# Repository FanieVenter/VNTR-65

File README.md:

# VNTR-65

A custom, over-engineered 65% keyboard featuring an RP2350 MCU, a hall effect key matrix, an analog slide potentiometer, and an OLED display. Built for daily use thanks to Hack Club.

## Why I decided to make this keyboard.
I wanted to build a nice keyboard that I could use every day at school while knowing it won't break, I also wanted to make a keyboard that used hall effect switches to allow for analog inputs in racing ganes like Assetto Corsa and giving me a more challenging and fun experience designing it.

## How to use it.
To use this keyboard you will need to either download the production files for JLCPCB or create your own by exporting it them from Kicad. You will then need to place a order for the PCB using the productions files at your chosen pcb manufacturer. After you have received the PCB you will need to solder all the components onto the PCB and then flash the firmware onto the RP2350. While this is happening you can either 3d print the case or get it milled out of aluminum and wood. After you have the case and the PCB ready you can then assemble the keyboard and upload the firmware to the RP2350 and then you can use it. 

## What I learnt with this project.
I learn't how to design a keyboard from scratch using Kicad for the pcb. I also learn't how to use onshape after deciding to swap to it from Freecad a little bit because the projects says to have it in onshape but mostly as I had realised after 2 years of FreeCAD use that it wasn't powerful enough for me. I learn't how to take a raw wood texture file and make it look like a satin polyeuranted finished piece of wood in blender.
# Important.
The cost of the pcba has gone down since I submitted the project for review. For updated pricing and screenshot check the [BOM](BOM.pdf).

## Onshape Link
Onshape link for the [Case](https://cad.onshape.com/documents/299d1cd18e1c0fa7ad37c188/w/39af968ec4536d8e3dda6814/e/b83c5326b9acf81a68bd5a35?renderMode=0&uiState=6a509a3fdb7545b8e7caa558).

## Files
- [Journal](Journal.md) Journal of this project.
- [PCB Files](Hardware/PCB) Kicad files for the keyboard.
- [Production Files](Hardware/PCB/production) Production files for this project.
- [3D Files](Hardware/3D%20Models) 3D models used in this project as well as where the blender file is.
- [Gallery](Gallery.md) Images of the project and renders of the keyboard.
- [BOM (PDF)](BOM.pdf) Bill of materials.
- [BOM (CSV)](BOM.csv) Bill of materials in CSV format.

## Schematic-Main

*Main schematic.*  

## Schematic-Switch

*Hall effect switch matrix.*

## PCB Photos

*Front and back of the PCB — the back has the silkscreen applied.*

## Wiring

*Full PCB wiring across all copper layers.*

*Full PCB wiring on the front copper layer.*

*Full PCB wiring on the back copper layer.*

*Main section wiring on the front copper layer.*

*Main section wiring on the back copper layer.*

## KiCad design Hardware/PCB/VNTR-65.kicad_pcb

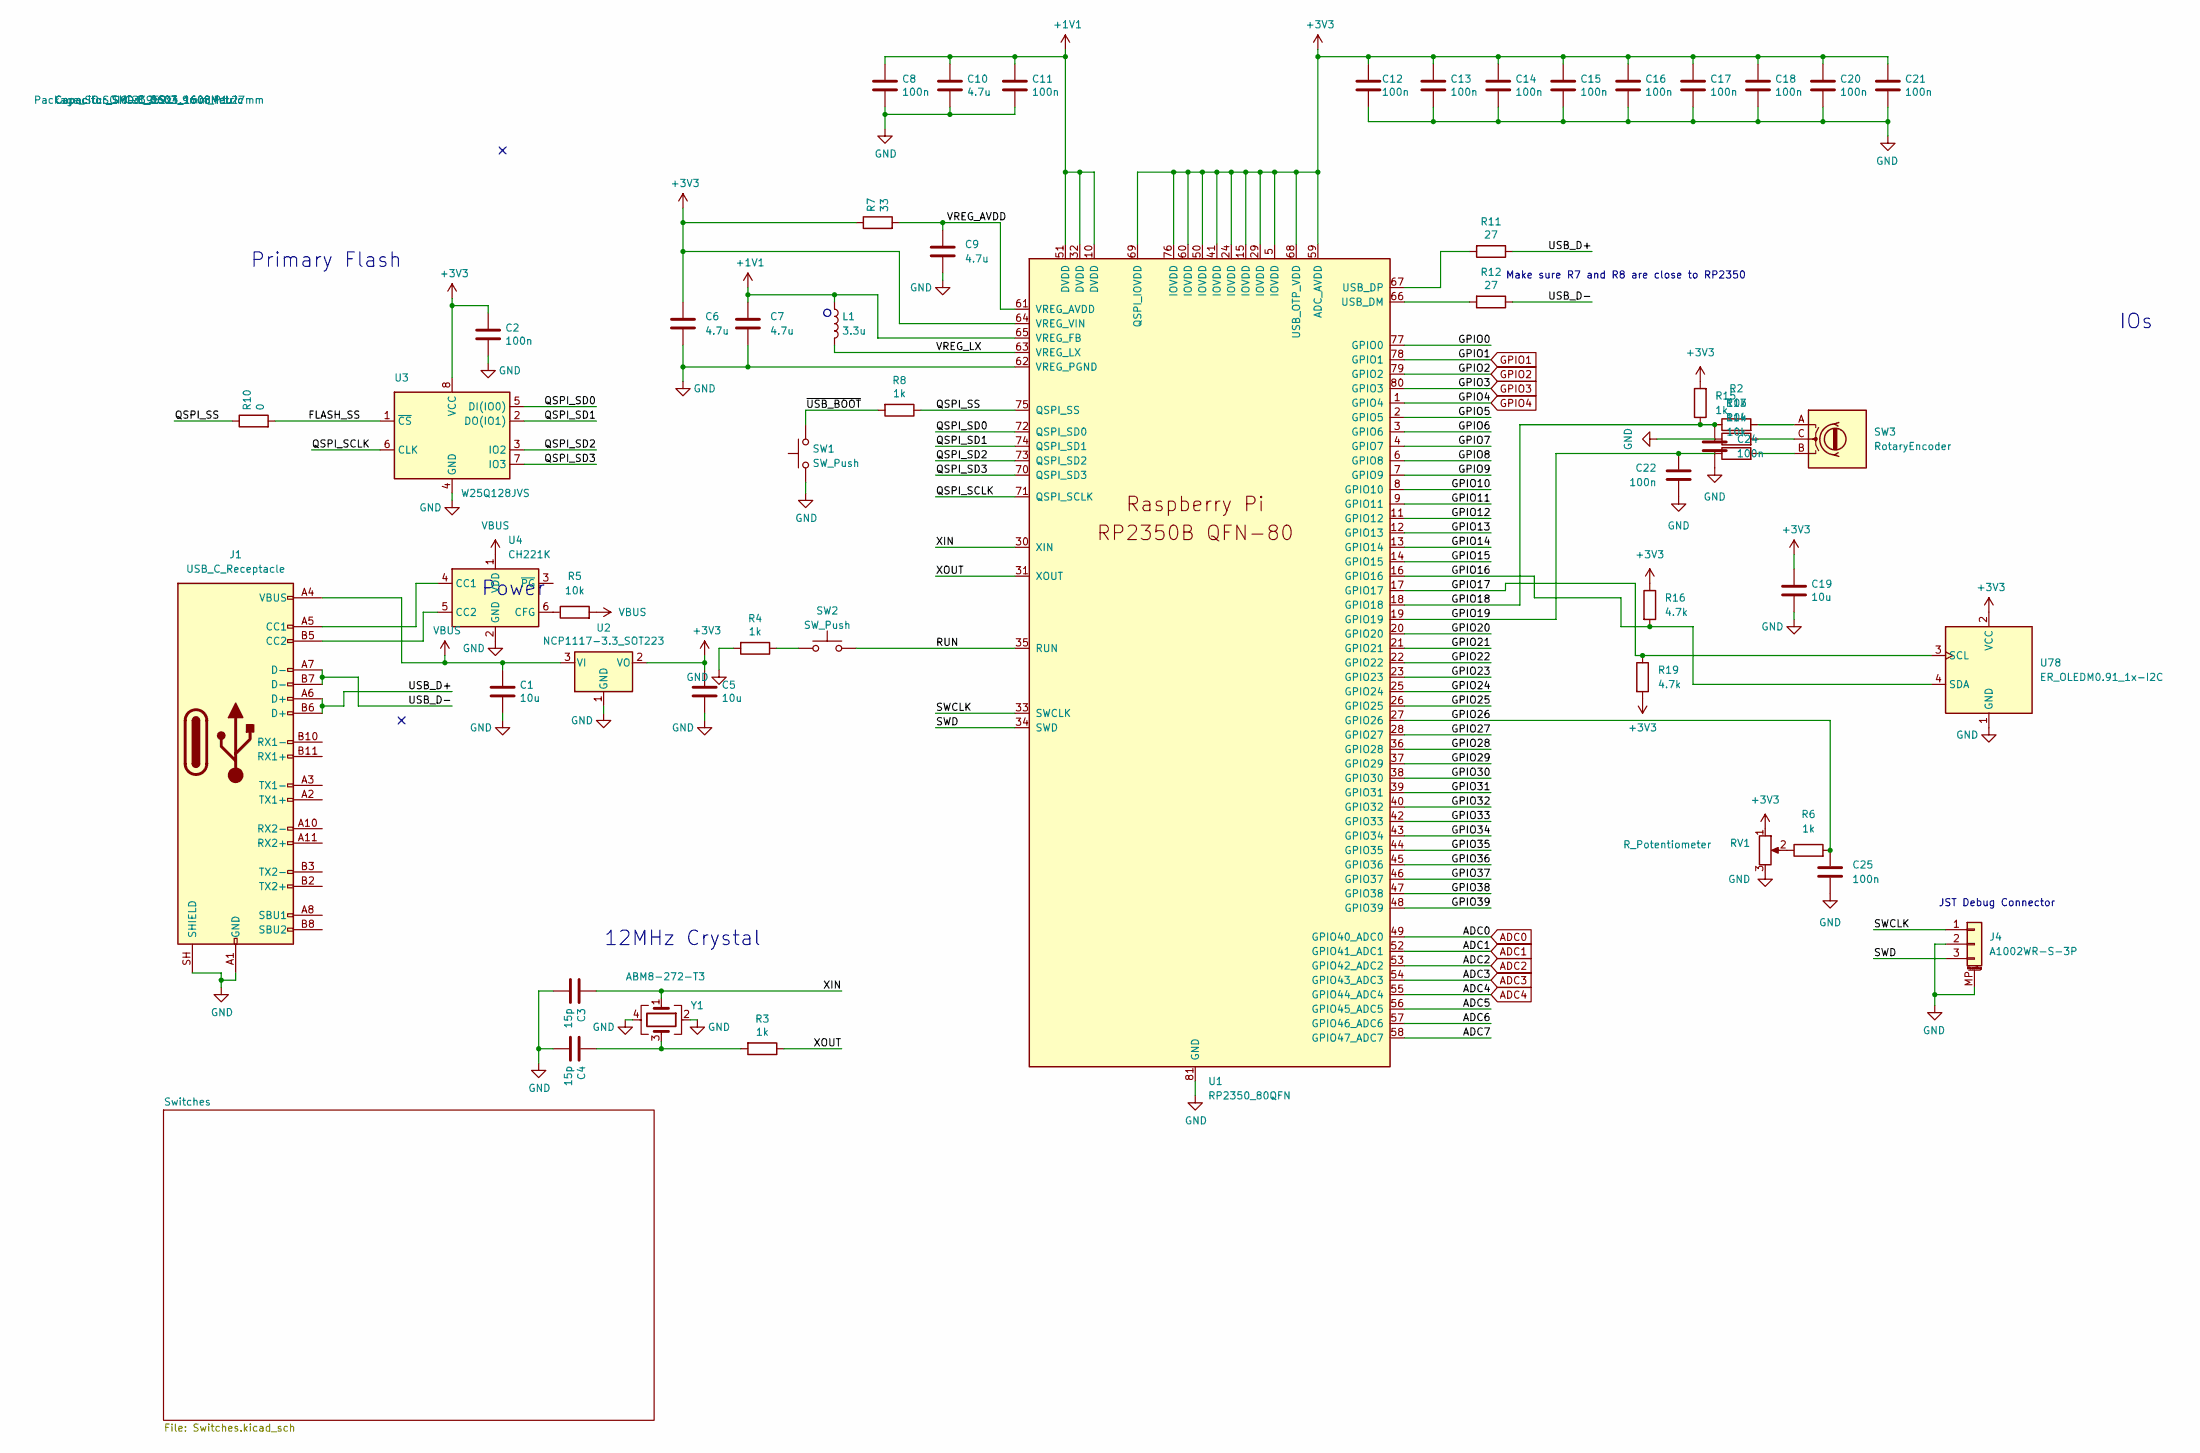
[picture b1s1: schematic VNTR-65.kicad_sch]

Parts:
C1, C5, C19: 10u; C_0603_1608Metric
C2, C8, C11, C12, C13, C14, C15, C16, C17, C18, C20, C21, C22, C24, C25: 100n; C_0603_1608Metric
C3, C4: 15p; C_0603_1608Metric
C6, C7, C9, C10: 4.7u; C_0603_1608Metric
J1: USB_C_Receptacle; USB_C_Receptacle_Amphenol_12401610E4-2A
J4: A1002WR-S-3P; JST_SH_SM03B-SRSS-TB_1x03-1MP_P1.00mm_Horizontal; LCSC Part # C239521
L1: 3.3u; L_pol_2016
R2, R5, R13, R14: 10k; R_0603_1608Metric
R3, R4, R6, R8, R15: 1k; R_0603_1608Metric
R7: 33; R_0603_1608Metric
R10: 0; R_0603_1608Metric
R11, R12: 27; R_0603_1608Metric
R16, R19: 4.7k; R_0603_1608Metric
RV1: R_Potentiometer; Potentiometer_Bourns_PTA6043_Single_Slide
SW1, SW2: SW_Push; SW_Push_1P1T_NO_Vertical_Wuerth_434133025816
SW3: RotaryEncoder; RotaryEncoder_Alps_EC11E-Switch_Vertical_H20mm
U1: RP2350_80QFN; QFN-80-1EP_10x10mm_P0.4mm_EP3.4x3.4mm
U2: NCP1117-3.3_SOT223; SOT-223-3_TabPin2
U3: W25Q128JVS; SOIC-8_3.9x4.9mm_P1.27mm
U4: CH221K; SOT-23-6
U78: ER_OLEDM0.91_1x-I2C
Y1: ABM8-272-T3; Crystal_SMD_3225-4Pin_3.2x2.5mm

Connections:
+1V1: C7.1, C8.1, C10.1, C11.1, L1.1, U1.10 (DVDD), U1.32 (DVDD), U1.51 (DVDD), U1.65 (VREG_FB)
+3V3: C2.1, C5.1, C6.1, C12.1, C13.1, C14.1, C15.1, C16.1, C17.1, C18.1, C19.1, C20.1, C21.1, R7.1, R15.2, R16.1, R19.2, RV1.1, U1.5 (IOVDD), U1.15 (IOVDD), U1.24 (IOVDD), U1.29 (IOVDD), U1.41 (IOVDD), U1.50 (IOVDD), U1.59 (ADC_AVDD), U1.60 (IOVDD), U1.64 (VREG_VIN), U1.68 (USB_OTP_VDD), U1.69 (QSPI_IOVDD), U1.76 (IOVDD), U2.2 (VO), U3.8 (VCC), U78.2 (VCC); also elsewhere on the board
/ADC5: U1.56 (GPIO45_ADC5)
/ADC6: U1.57 (GPIO46_ADC6)
/ADC7: U1.58 (GPIO47_ADC7)
/FLASH_SS: R10.2, U3.1 (~CS); also elsewhere on the board
/GPIO0: U1.77 (GPIO0); also elsewhere on the board
/GPIO5: U1.2 (GPIO5)
/GPIO6: U1.3 (GPIO6)
/GPIO7: U1.4 (GPIO7)
/GPIO8: U1.6 (GPIO8)
/GPIO9: U1.7 (GPIO9)
/GPIO10: U1.8 (GPIO10)
/GPIO11: U1.9 (GPIO11)
/GPIO12: U1.11 (GPIO12)
/GPIO13: U1.12 (GPIO13)
/GPIO14: U1.13 (GPIO14)
/GPIO15: U1.14 (GPIO15)
/GPIO16: R16.2, U1.16 (GPIO16), U78.4 (SDA)
/GPIO17: R19.1, U1.17 (GPIO17), U78.3 (SCL)
/GPIO18: C24.2, R2.1, R15.1, U1.18 (GPIO18)
/GPIO19: C22.2, R14.1, U1.19 (GPIO19)
/GPIO20: U1.20 (GPIO20)
/GPIO21: U1.21 (GPIO21)
/GPIO22: U1.22 (GPIO22)
/GPIO23: U1.23 (GPIO23)
/GPIO24: U1.25 (GPIO24)
/GPIO25: U1.26 (GPIO25)
/GPIO26: C25.2, R6.2, U1.27 (GPIO26)
/GPIO27: U1.28 (GPIO27)
/GPIO28: U1.36 (GPIO28)
/GPIO29: U1.37 (GPIO29)
/GPIO30: U1.38 (GPIO30)
/GPIO31: U1.39 (GPIO31)
/GPIO32: U1.40 (GPIO32)
/GPIO33: U1.42 (GPIO33)
/GPIO34: U1.43 (GPIO34)
/GPIO35: U1.44 (GPIO35)
/GPIO36: U1.45 (GPIO36)
/GPIO37: U1.46 (GPIO37)
/GPIO38: U1.47 (GPIO38)
/GPIO39: U1.48 (GPIO39)
/QSPI_SCLK: U1.71 (QSPI_SCLK), U3.6 (CLK)
/QSPI_SD0: U1.72 (QSPI_SD0), U3.5 (DI(IO0))
/QSPI_SD1: U1.74 (QSPI_SD1), U3.2 (DO(IO1))
/QSPI_SD2: U1.73 (QSPI_SD2), U3.3 (IO2)
/QSPI_SD3: U1.70 (QSPI_SD3), U3.7 (IO3)
/QSPI_SS: R8.1, R10.1, U1.75 (QSPI_SS)
/RUN: SW2.2, U1.35 (RUN)
/SWCLK: J4.1, U1.33 (SWCLK)
/SWD: J4.3, U1.34 (SWD)
/USB_D+: J1.A6 (D+), J1.B6 (D+), R11.1
/USB_D-: J1.A7 (D-), J1.B7 (D-), R12.1
/VREG_AVDD: C9.1, R7.2, U1.61 (VREG_AVDD)
/VREG_LX: L1.2, U1.63 (VREG_LX)
/XIN: C3.1, U1.30 (XIN), Y1.1
/XOUT: R3.1, U1.31 (XOUT)
/~USB_BOOT: R8.2, SW1.2
ADC0: U1.49 (GPIO40_ADC0); also elsewhere on the board
ADC1: U1.52 (GPIO41_ADC1); also elsewhere on the board
ADC2: U1.53 (GPIO42_ADC2); also elsewhere on the board
ADC3: U1.54 (GPIO43_ADC3); also elsewhere on the board
ADC4: U1.55 (GPIO44_ADC4); also elsewhere on the board
GND: C1.2, C2.2, C3.2, C4.2, C5.2, C6.2, C7.2, C8.2, C9.2, C10.2, C11.2, C12.2, C13.2, C14.2, C15.2, C16.2, C17.2, C18.2, C19.2, C20.2, C21.2, C22.1, C24.1, C25.1, J1.A1 (GND), J1.A12 (GND), J1.B1 (GND), J1.B12 (GND), J1.SH (SHIELD), J4.2, J4.MP (MountPin), R4.2, R13.1, RV1.3, SW1.1, U1.62 (VREG_PGND), U1.81 (GND), U2.1 (GND), U3.4 (GND), U4.2 (GND), U78.1 (GND), Y1.2, Y1.4; also elsewhere on the board
GPIO1: U1.78 (GPIO1); also elsewhere on the board
GPIO2: U1.79 (GPIO2); also elsewhere on the board
GPIO3: U1.80 (GPIO3); also elsewhere on the board
GPIO4: U1.1 (GPIO4); also elsewhere on the board
unnamed: C4.1, R3.2, Y1.3
unnamed: J1.A5 (CC1), U4.4 (CC1)
unnamed: J1.B5 (CC2), U4.5 (CC2)
unnamed: R2.2, SW3.A
unnamed: R4.1, SW2.1
unnamed: R6.1, RV1.2
unnamed: R13.2, SW3.C
unnamed: R14.2, SW3.B
unnamed: R12.2, U1.66 (USB_DM)
unnamed: R11.2, U1.67 (USB_DP)
unnamed: R5.1, U4.6 (CFG)
VBUS: C1.1, J1.A4 (VBUS), J1.A9 (VBUS), J1.B4 (VBUS), J1.B9 (VBUS), R5.2, U2.3 (VI), U4.1 (VDD)

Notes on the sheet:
Make sure R7 and R8 are close to RP2350
JST Debug Connector
Power
12MHz Crystal
IOs
Primary Flash

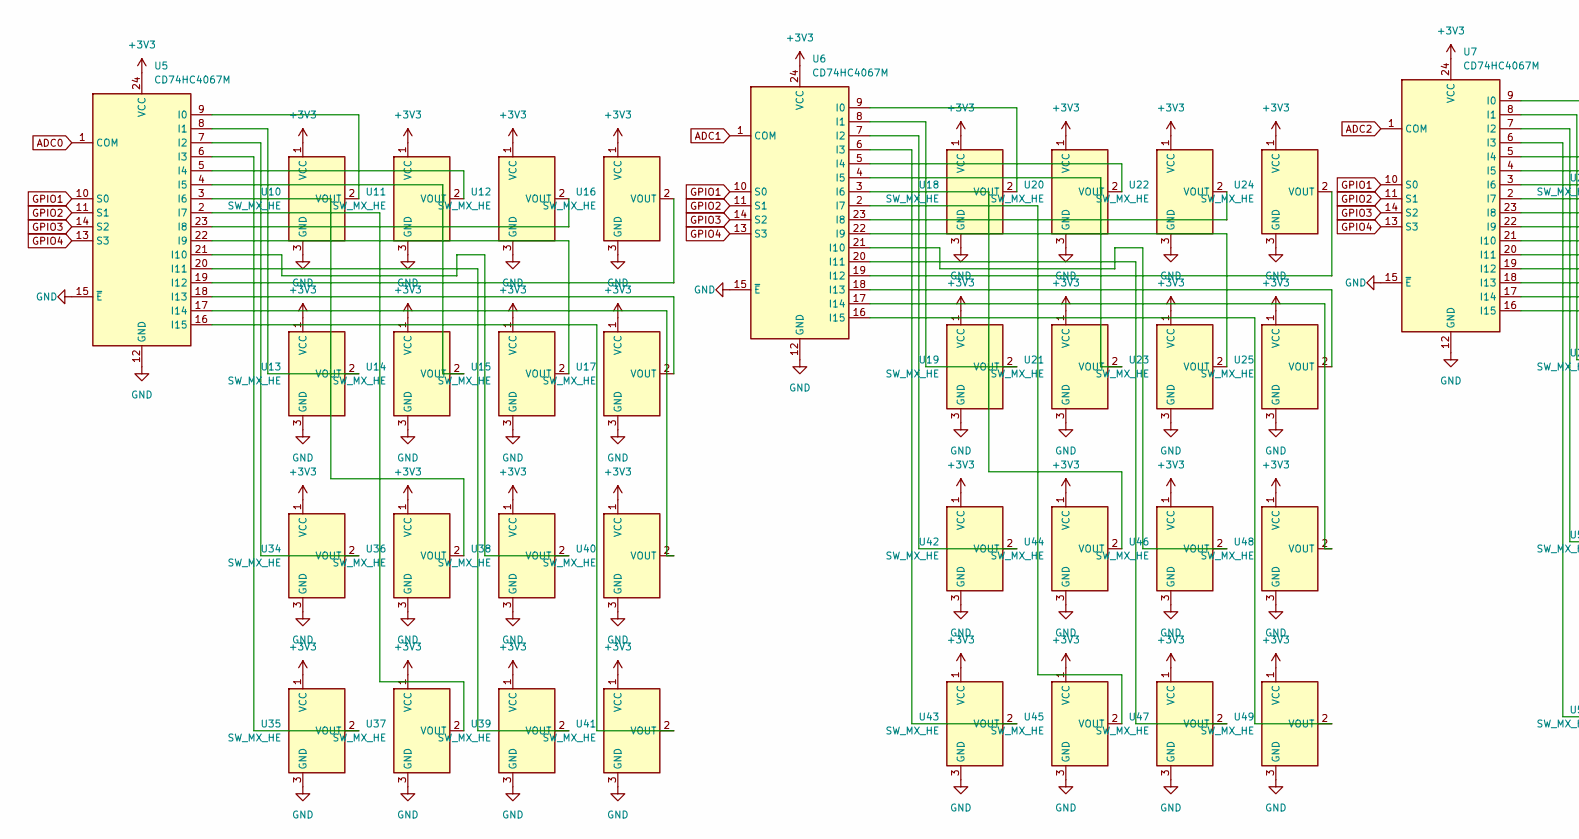
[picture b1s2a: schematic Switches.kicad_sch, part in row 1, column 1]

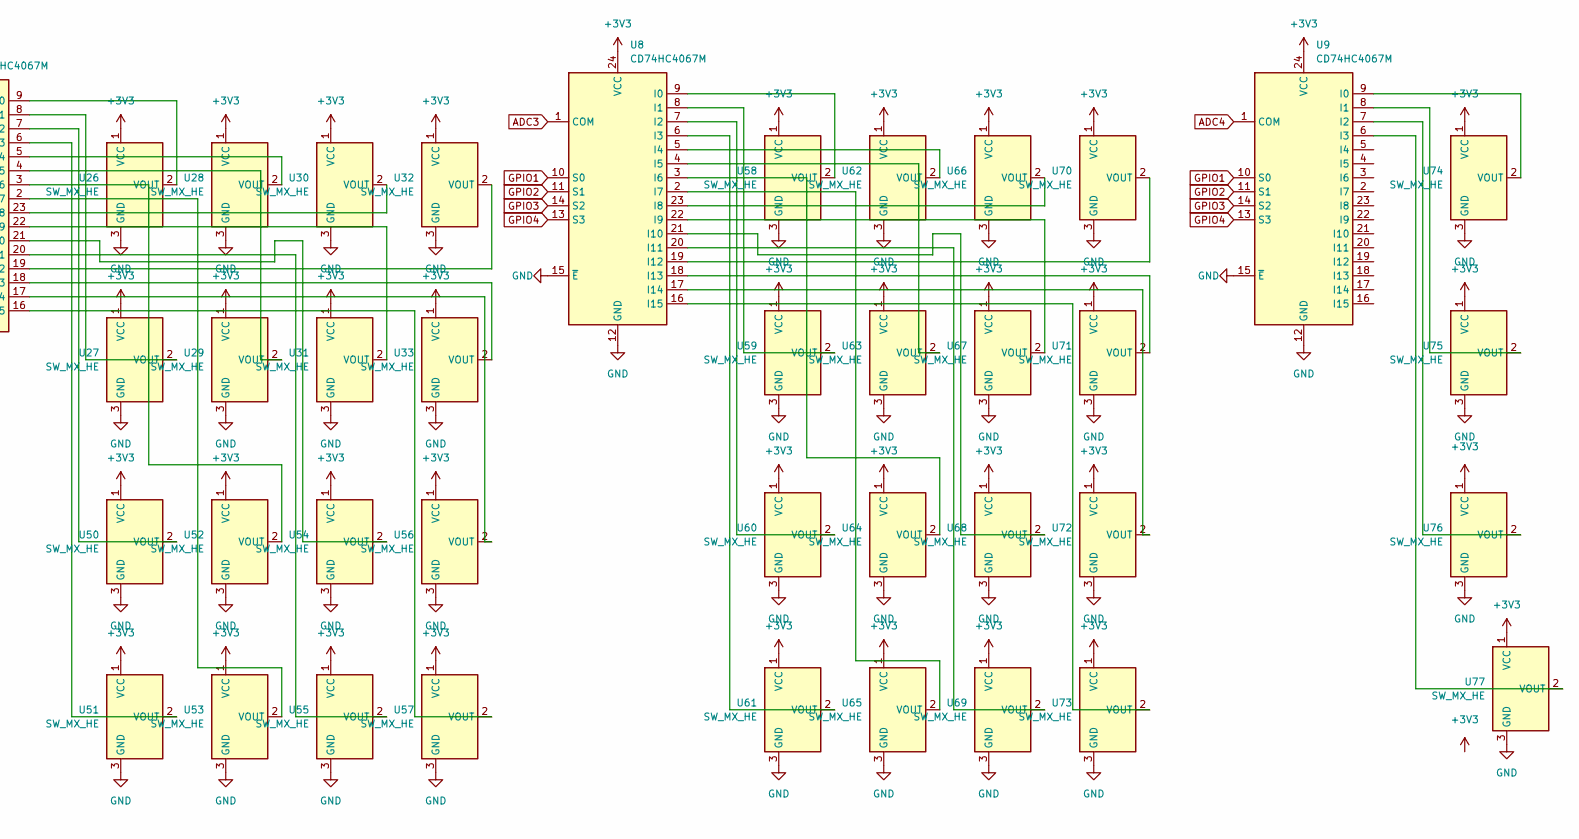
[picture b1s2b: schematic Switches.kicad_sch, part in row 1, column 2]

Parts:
U5, U6, U7, U8, U9: CD74HC4067M; SOIC-24W_7.5x15.4mm_P1.27mm
U10, U11, U12, U13, U14, U15, U16, U17, U18, U19, U20, U21, U22, U23, U24, U25, U26, U27, U28, U29, U30, U31, U32, U33, U34, U35, U36, U37, U38, U39, U40, U41, U42, U43, U44, U45, U46, U47, U48, U49, U50, U51, U52, U53, U54, U55, U56, U57, U58, U59, U60, U61, U62, U63, U64, U65, U66, U67, U68, U69, U70, U71, U72, U73, U74, U75, U76, U77: SW_MX_HE; SW_MX_HE_0deg_1u

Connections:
+3V3: U5.24 (VCC), U6.24 (VCC), U7.24 (VCC), U8.24 (VCC), U9.24 (VCC), U10.1 (VCC), U11.1 (VCC), U12.1 (VCC), U13.1 (VCC), U14.1 (VCC), U15.1 (VCC), U16.1 (VCC), U17.1 (VCC), U18.1 (VCC), U19.1 (VCC), U20.1 (VCC), U21.1 (VCC), U22.1 (VCC), U23.1 (VCC), U24.1 (VCC), U25.1 (VCC), U26.1 (VCC), U27.1 (VCC), U28.1 (VCC), U29.1 (VCC), U30.1 (VCC), U31.1 (VCC), U32.1 (VCC), U33.1 (VCC), U34.1 (VCC), U35.1 (VCC), U36.1 (VCC), U37.1 (VCC), U38.1 (VCC), U39.1 (VCC), U40.1 (VCC), U41.1 (VCC), U42.1 (VCC), U43.1 (VCC), U44.1 (VCC), U45.1 (VCC), U46.1 (VCC), U47.1 (VCC), U48.1 (VCC), U49.1 (VCC), U50.1 (VCC), U51.1 (VCC), U52.1 (VCC), U53.1 (VCC), U54.1 (VCC), U55.1 (VCC), U56.1 (VCC), U57.1 (VCC), U58.1 (VCC), U59.1 (VCC), U60.1 (VCC), U61.1 (VCC), U62.1 (VCC), U63.1 (VCC), U64.1 (VCC), U65.1 (VCC), U66.1 (VCC), U67.1 (VCC), U68.1 (VCC), U69.1 (VCC), U70.1 (VCC), U71.1 (VCC), U72.1 (VCC), U73.1 (VCC), U74.1 (VCC), U75.1 (VCC), U76.1 (VCC), U77.1 (VCC); also elsewhere on the board
ADC0: U5.1 (COM); also elsewhere on the board
ADC1: U6.1 (COM); also elsewhere on the board
ADC2: U7.1 (COM); also elsewhere on the board
ADC3: U8.1 (COM); also elsewhere on the board
ADC4: U9.1 (COM); also elsewhere on the board
GND: U5.12 (GND), U5.15 (~E), U6.12 (GND), U6.15 (~E), U7.12 (GND), U7.15 (~E), U8.12 (GND), U8.15 (~E), U9.12 (GND), U9.15 (~E), U10.3 (GND), U11.3 (GND), U12.3 (GND), U13.3 (GND), U14.3 (GND), U15.3 (GND), U16.3 (GND), U17.3 (GND), U18.3 (GND), U19.3 (GND), U20.3 (GND), U21.3 (GND), U22.3 (GND), U23.3 (GND), U24.3 (GND), U25.3 (GND), U26.3 (GND), U27.3 (GND), U28.3 (GND), U29.3 (GND), U30.3 (GND), U31.3 (GND), U32.3 (GND), U33.3 (GND), U34.3 (GND), U35.3 (GND), U36.3 (GND), U37.3 (GND), U38.3 (GND), U39.3 (GND), U40.3 (GND), U41.3 (GND), U42.3 (GND), U43.3 (GND), U44.3 (GND), U45.3 (GND), U46.3 (GND), U47.3 (GND), U48.3 (GND), U49.3 (GND), U50.3 (GND), U51.3 (GND), U52.3 (GND), U53.3 (GND), U54.3 (GND), U55.3 (GND), U56.3 (GND), U57.3 (GND), U58.3 (GND), U59.3 (GND), U60.3 (GND), U61.3 (GND), U62.3 (GND), U63.3 (GND), U64.3 (GND), U65.3 (GND), U66.3 (GND), U67.3 (GND), U68.3 (GND), U69.3 (GND), U70.3 (GND), U71.3 (GND), U72.3 (GND), U73.3 (GND), U74.3 (GND), U75.3 (GND), U76.3 (GND), U77.3 (GND); also elsewhere on the board
GPIO1: U5.10 (S0), U6.10 (S0), U7.10 (S0), U8.10 (S0), U9.10 (S0); also elsewhere on the board
GPIO2: U5.11 (S1), U6.11 (S1), U7.11 (S1), U8.11 (S1), U9.11 (S1); also elsewhere on the board
GPIO3: U5.14 (S2), U6.14 (S2), U7.14 (S2), U8.14 (S2), U9.14 (S2); also elsewhere on the board
GPIO4: U5.13 (S3), U6.13 (S3), U7.13 (S3), U8.13 (S3), U9.13 (S3); also elsewhere on the board
unnamed: U5.9 (I0), U10.2 (VOUT)
unnamed: U5.5 (I4), U11.2 (VOUT)
unnamed: U5.23 (I8), U12.2 (VOUT)
unnamed: U5.8 (I1), U13.2 (VOUT)
unnamed: U5.4 (I5), U14.2 (VOUT)
unnamed: U5.22 (I9), U15.2 (VOUT)
unnamed: U5.19 (I12), U16.2 (VOUT)
unnamed: U5.18 (I13), U17.2 (VOUT)
unnamed: U6.9 (I0), U18.2 (VOUT)
unnamed: U6.8 (I1), U19.2 (VOUT)
unnamed: U6.5 (I4), U20.2 (VOUT)
unnamed: U6.4 (I5), U21.2 (VOUT)
unnamed: U6.23 (I8), U22.2 (VOUT)
unnamed: U6.22 (I9), U23.2 (VOUT)
unnamed: U6.19 (I12), U24.2 (VOUT)
unnamed: U6.18 (I13), U25.2 (VOUT)
unnamed: U7.9 (I0), U26.2 (VOUT)
unnamed: U7.8 (I1), U27.2 (VOUT)
unnamed: U7.5 (I4), U28.2 (VOUT)
unnamed: U7.4 (I5), U29.2 (VOUT)
unnamed: U7.23 (I8), U30.2 (VOUT)
unnamed: U7.22 (I9), U31.2 (VOUT)
unnamed: U7.19 (I12), U32.2 (VOUT)
unnamed: U7.18 (I13), U33.2 (VOUT)
unnamed: U5.7 (I2), U34.2 (VOUT)
unnamed: U5.6 (I3), U35.2 (VOUT)
unnamed: U5.3 (I6), U36.2 (VOUT)
unnamed: U5.2 (I7), U37.2 (VOUT)
unnamed: U5.21 (I10), U38.2 (VOUT)
unnamed: U5.20 (I11), U39.2 (VOUT)
unnamed: U5.17 (I14), U40.2 (VOUT)
unnamed: U5.16 (I15), U41.2 (VOUT)
unnamed: U6.7 (I2), U42.2 (VOUT)
unnamed: U6.6 (I3), U43.2 (VOUT)
unnamed: U6.3 (I6), U44.2 (VOUT)
unnamed: U6.2 (I7), U45.2 (VOUT)
unnamed: U6.21 (I10), U46.2 (VOUT)
unnamed: U6.20 (I11), U47.2 (VOUT)
unnamed: U6.17 (I14), U48.2 (VOUT)
unnamed: U6.16 (I15), U49.2 (VOUT)
unnamed: U7.7 (I2), U50.2 (VOUT)
unnamed: U7.6 (I3), U51.2 (VOUT)
unnamed: U7.3 (I6), U52.2 (VOUT)
unnamed: U7.2 (I7), U53.2 (VOUT)
unnamed: U7.21 (I10), U54.2 (VOUT)
unnamed: U7.20 (I11), U55.2 (VOUT)
unnamed: U7.17 (I14), U56.2 (VOUT)
unnamed: U7.16 (I15), U57.2 (VOUT)
unnamed: U8.9 (I0), U58.2 (VOUT)
unnamed: U8.8 (I1), U59.2 (VOUT)
unnamed: U8.7 (I2), U60.2 (VOUT)
unnamed: U8.6 (I3), U61.2 (VOUT)
unnamed: U8.5 (I4), U62.2 (VOUT)
unnamed: U8.4 (I5), U63.2 (VOUT)
unnamed: U8.3 (I6), U64.2 (VOUT)
unnamed: U8.2 (I7), U65.2 (VOUT)
unnamed: U8.23 (I8), U66.2 (VOUT)
unnamed: U8.22 (I9), U67.2 (VOUT)
unnamed: U8.21 (I10), U68.2 (VOUT)
unnamed: U8.20 (I11), U69.2 (VOUT)
unnamed: U8.19 (I12), U70.2 (VOUT)
unnamed: U8.18 (I13), U71.2 (VOUT)
unnamed: U8.17 (I14), U72.2 (VOUT)
unnamed: U8.16 (I15), U73.2 (VOUT)
unnamed: U9.9 (I0), U74.2 (VOUT)
unnamed: U9.8 (I1), U75.2 (VOUT)
unnamed: U9.7 (I2), U76.2 (VOUT)
unnamed: U9.6 (I3), U77.2 (VOUT)

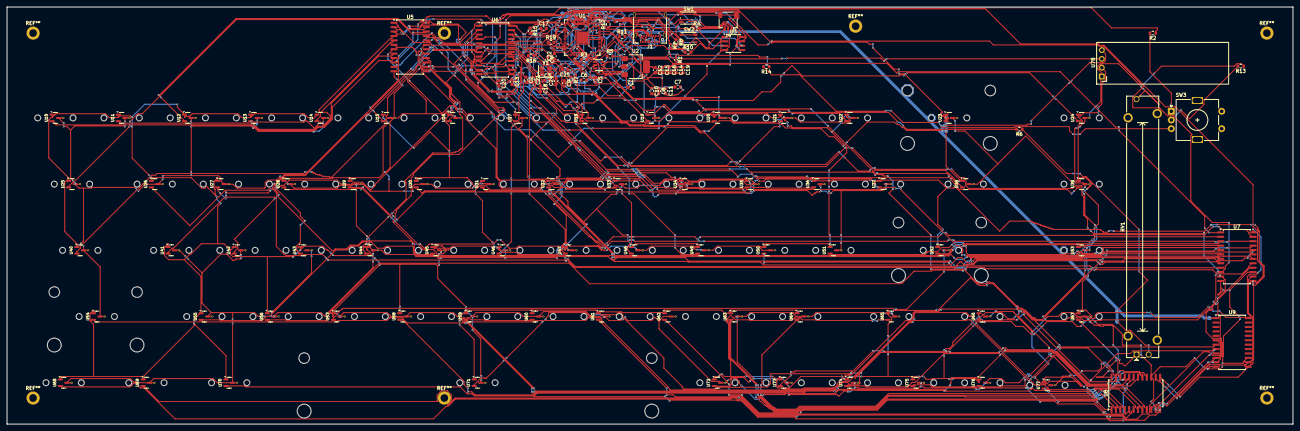
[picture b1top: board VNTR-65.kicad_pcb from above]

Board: 2 copper layers, 370.0 x 120.0 mm, 126 parts (0 on the bottom side), 114 nets.

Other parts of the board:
R1, R9: DNF; R_0402_1005Metric

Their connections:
+3V3: R1.1; also elsewhere on the board
/FLASH_SS: R1.2, R9.2; also elsewhere on the board
/GPIO0: R9.1; also elsewhere on the board

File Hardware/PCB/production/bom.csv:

"Designator","Footprint","Quantity","Value","LCSC Part #"
"C1,C5,C19","Capacitor_SMD:C_0603_1608Metric","3","10u",""
"C2,C8,C11-C18,C20-C22,C24,C25","Capacitor_SMD:C_0603_1608Metric","15","100n",""
"C3,C4","Capacitor_SMD:C_0603_1608Metric","2","15p",""
"C6,C7,C9,C10","Capacitor_SMD:C_0603_1608Metric","4","4.7u",""
"J1","Connector_USB:USB_C_Receptacle_Amphenol_12401610E4-2A","1","USB_C_Receptacle",""
"J4","Connector_JST:JST_SH_SM03B-SRSS-TB_1x03-1MP_P1.00mm_Horizontal","1","A1002WR-S-3P","C239521"
"L1","RP2350_80QFN_minimal:L_pol_2016","1","3.3u",""
"R2,R5,R13,R14","Resistor_SMD:R_0603_1608Metric","4","10k",""
"R3,R4,R6,R8,R15","Resistor_SMD:R_0603_1608Metric","5","1k",""
"R7","Resistor_SMD:R_0603_1608Metric","1","33",""
"R10","Resistor_SMD:R_0603_1608Metric","1","0",""
"R11,R12","Resistor_SMD:R_0603_1608Metric","2","27",""
"R16,R19","Resistor_SMD:R_0603_1608Metric","2","4.7k",""
"RV1","PCM_Potentiometer_THT_AKL:Potentiometer_Bourns_PTA6043_Single_Slide","1","R_Potentiometer",""
"SW1,SW2","Button_Switch_SMD:SW_Push_1P1T_NO_Vertical_Wuerth_434133025816","2","SW_Push",""
"SW3","Rotary_Encoder:RotaryEncoder_Alps_EC11E-Switch_Vertical_H20mm","1","RotaryEncoder",""
"U1","Package_DFN_QFN:QFN-80-1EP_10x10mm_P0.4mm_EP3.4x3.4mm","1","RP2350_80QFN",""
"U2","Package_TO_SOT_SMD:SOT-223-3_TabPin2","1","NCP1117-3.3_SOT223",""
"U3","Package_SO:SOIC-8_3.9x4.9mm_P1.27mm","1","W25Q128JVS",""
"U4","Package_TO_SOT_SMD:SOT-23-6","1","CH221K",""
"U5-U9","Package_SO:SOIC-24W_7.5x15.4mm_P1.27mm","5","CD74HC4067M",""
"U10-U77","PCM_marbastlib-he:SW_MX_HE_0deg_1u","68","SW_MX_HE",""
"U78","Display:ER_OLEDM0.91_1x-I2C","1","ER_OLEDM0.91_1x-I2C",""
"Y1","Crystal:Crystal_SMD_3225-4Pin_3.2x2.5mm","1","ABM8-272-T3",""
